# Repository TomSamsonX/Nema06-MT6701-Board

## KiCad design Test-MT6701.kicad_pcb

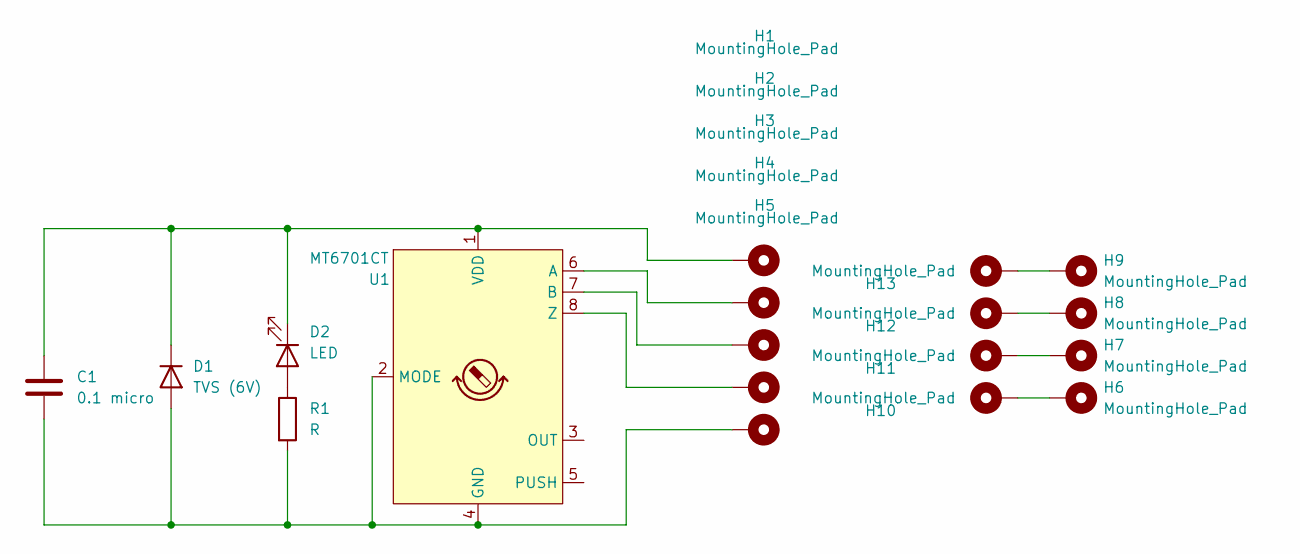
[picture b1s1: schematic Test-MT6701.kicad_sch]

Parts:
C1: 0.1 micro; C_0603_1608Metric
D1: TVS (6V); D_SOD-123
D2: LED; LED_0603_1608Metric
H1, H2, H3, H4, H5, H6, H7, H8, H9, H10, H11, H12, H13: MountingHole_Pad; TestPoint_Pad_D1.0mm
R1: R; R_0603_1608Metric_Pad0.98x0.95mm_HandSolder
U1: MT6701CT; SO-8_3.9x4.9mm_P1.27mm

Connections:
unnamed 0: C1.2, D1.2 (A), H5.1 (1_1), R1.2, U1.2 (MODE), U1.4 (GND); also elsewhere on the board
unnamed 1: C1.1, D1.1 (K), D2.1 (K), H1.1 (1_1), U1.1 (VDD); also elsewhere on the board
unnamed: D2.2 (A), R1.1
unnamed: H6.1 (1_1), H10.1 (1_1)
unnamed: H7.1 (1_1), H11.1 (1_1)
unnamed: H8.1 (1_1), H12.1 (1_1)
unnamed: H9.1 (1_1), H13.1 (1_1)
unnamed 7: H2.1 (1_1), U1.6 (A); also elsewhere on the board
unnamed 8: H3.1 (1_1), U1.7 (B); also elsewhere on the board
unnamed 9: H4.1 (1_1), U1.8 (Z); also elsewhere on the board

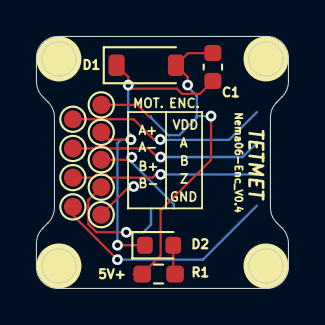
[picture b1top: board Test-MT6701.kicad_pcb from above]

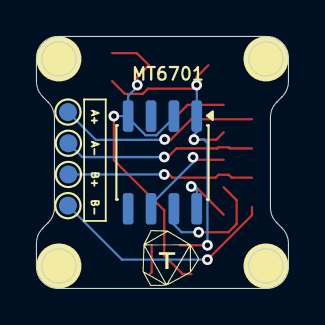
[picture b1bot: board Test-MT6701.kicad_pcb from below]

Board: 4 copper layers, 14.0 x 14.0 mm, 18 parts (5 on the bottom side), 10 nets.

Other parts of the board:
MT6701: MT6701CT; SO-8_3.9x4.9mm_P1.27mm

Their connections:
unnamed 0: MT6701.2 (MODE), MT6701.4 (GND); also elsewhere on the board
unnamed 1: MT6701.1 (VDD); also elsewhere on the board
unnamed 7: MT6701.6 (A); also elsewhere on the board
unnamed 8: MT6701.7 (B); also elsewhere on the board
unnamed 9: MT6701.8 (Z); also elsewhere on the board
